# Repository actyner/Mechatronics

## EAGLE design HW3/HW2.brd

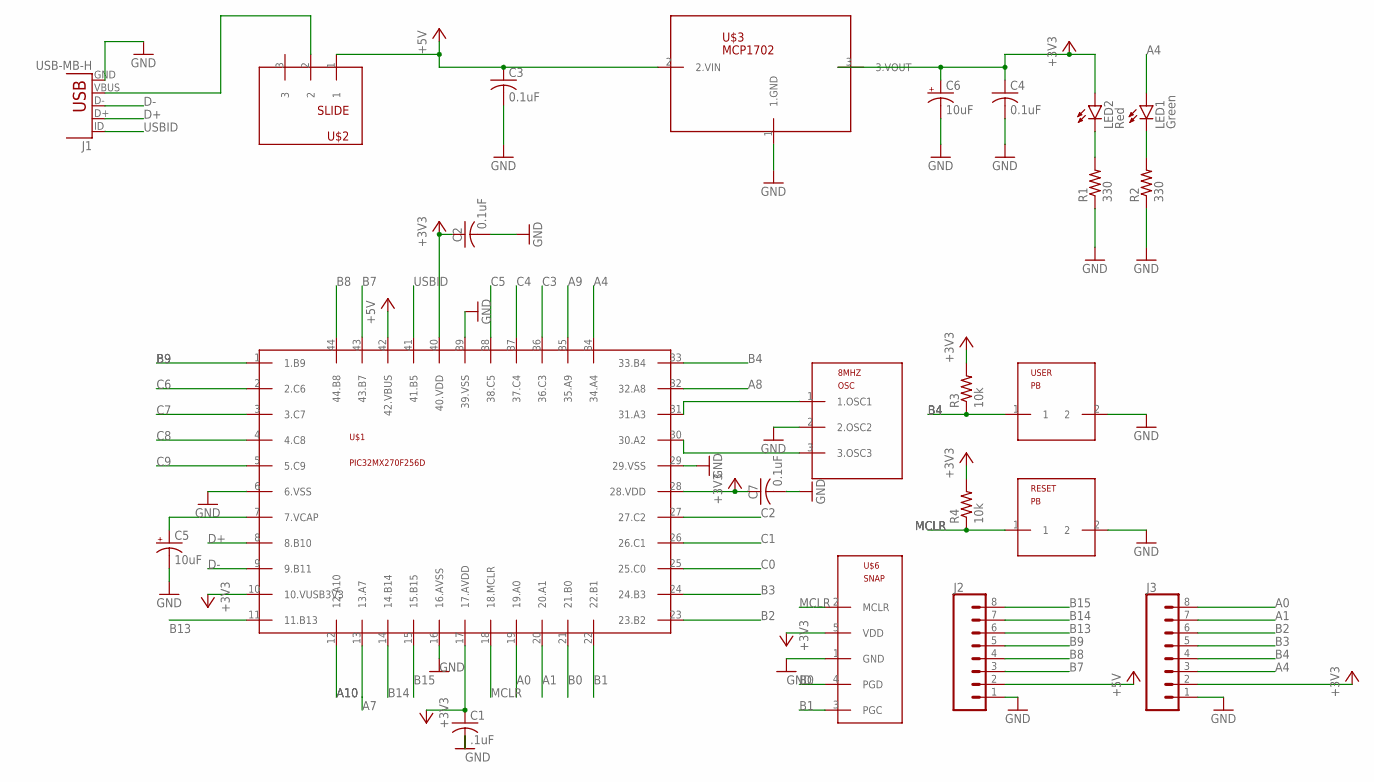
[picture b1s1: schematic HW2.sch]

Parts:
8MHZ: OSC
C1: .1uF; C025-025X050
C2, C3, C4, C7: 0.1uF; C025-025X050
C5, C6: 10uF; B45181B
J1: USB-MB-H
J2, J3: CONN_08
LED1: Green; LED3MM
LED2: Red; LED3MM
R1, R2: 330; 0207/10
R3, R4: 10k; 0207/10
RESET: PB
U$1: PIC32MX270F256D; MQFP44-2
U$2: SLIDE
U$3: MCP1702; TO92
U$6: SNAP; 1X05
USER: PB

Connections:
+3V3: C1.1, C2.1, C4.1, C6.+, C7.1, J3.2, LED2.A, R3.2, R4.2, U$1.10 (10.VUSB3V3), U$1.17 (17.AVDD), U$1.28 (28.VDD), U$1.40 (40.VDD), U$3.3 (3.VOUT), U$6.5 (VDD)
+5V: C3.1, J2.2, U$1.42 (42.VBUS), U$2.1, U$3.2 (2.VIN)
A0: J3.8, U$1.19 (19.A0)
A1: J3.7, U$1.20 (20.A1)
A4: J3.3, LED1.A, U$1.34 (34.A4)
A7: U$1.13 (13.A7)
A8: U$1.32 (32.A8)
A9: U$1.35 (35.A9)
A10: U$1.12 (12.A10)
B0: U$1.21 (21.B0), U$6.4 (PGD)
B1: U$1.22 (22.B1), U$6.3 (PGC)
B2: J3.6, U$1.23 (23.B2)
B3: J3.5, U$1.24 (24.B3)
B4: J3.4, R3.1, U$1.33 (33.B4), USER.1
B7: J2.3, U$1.43 (43.B7)
B8: J2.4, U$1.44 (44.B8)
B9: J2.5, U$1.1 (1.B9)
B13: J2.6, U$1.11 (11.B13)
B14: J2.7, U$1.14 (14.B14)
B15: J2.8, U$1.15 (15.B15)
C0: U$1.25 (25.C0)
C1: U$1.26 (26.C1)
C2: U$1.27 (27.C2)
C3: U$1.36 (36.C3)
C4: U$1.37 (37.C4)
C5: U$1.38 (38.C5)
C6: U$1.2 (2.C6)
C7: U$1.3 (3.C7)
C8: U$1.4 (4.C8)
C9: U$1.5 (5.C9)
D+: J1.D+, U$1.8 (8.B10)
D-: J1.D-, U$1.9 (9.B11)
GND: 8MHZ.2 (2.OSC2), C1.2, C2.2, C3.2, C4.2, C5.-, C6.-, C7.2, J1.GND, J2.1, J3.1, R1.1, R2.1, RESET.2, U$1.6 (6.VSS), U$1.16 (16.AVSS), U$1.29 (29.VSS), U$1.39 (39.VSS), U$3.1 (1.GND), U$6.1 (GND), USER.2
MCLR: R4.1, RESET.1, U$1.18 (18.MCLR), U$6.2 (MCLR)
unnamed: J1.VBUS, U$2.2
unnamed: LED2.K (C), R1.2
unnamed: 8MHZ.1 (1.OSC1), U$1.31 (31.A3)
unnamed: 8MHZ.3 (3.OSC3), U$1.30 (30.A2)
unnamed: C5.+, U$1.7 (7.VCAP)
unnamed: LED1.K (C), R2.2
USBID: J1.ID, U$1.41 (41.B5)

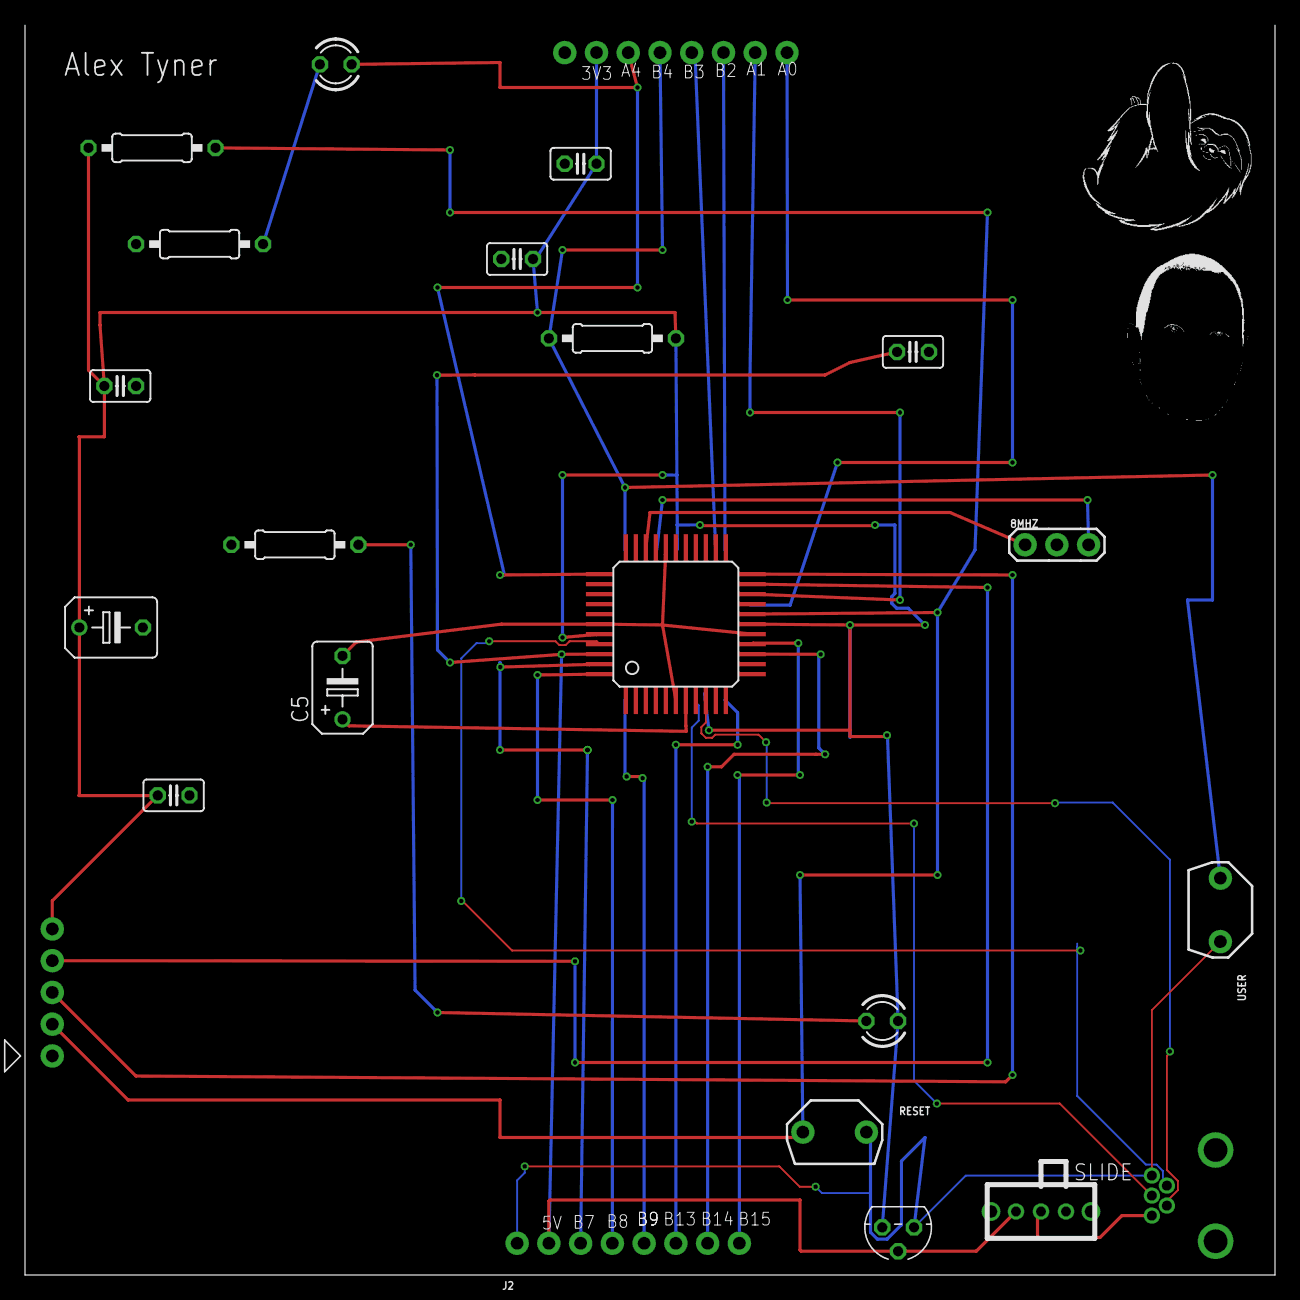
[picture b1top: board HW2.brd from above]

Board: 2 copper layers, 100.0 x 100.0 mm, 23 parts (0 on the bottom side), 27 nets.

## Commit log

2019-04-02 Code_with_PRAGMA.md
2019-04-04 Update Code
2019-04-04 Rename HW1/Code to HW1/HW1/Code
2019-04-08 Create HW2
2019-04-15 Create code
2019-05-20 Create design
2019-05-30 Create hw3
2019-06-03 Create hw15
2019-06-14 Create HW16
